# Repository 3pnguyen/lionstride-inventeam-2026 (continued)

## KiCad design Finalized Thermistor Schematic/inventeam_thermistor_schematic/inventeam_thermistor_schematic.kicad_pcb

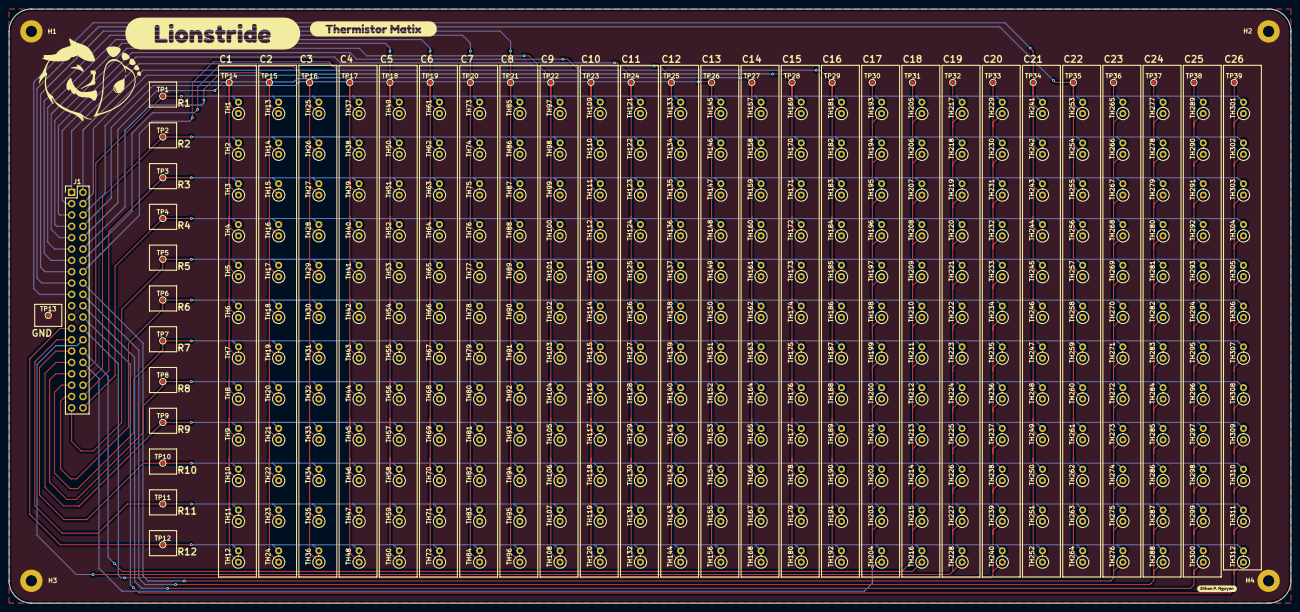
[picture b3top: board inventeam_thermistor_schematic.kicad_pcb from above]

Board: 2 copper layers, 287.0 x 133.0 mm, 359 parts (0 on the bottom side), 39 nets.

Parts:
H1, H2, H3, H4: Mounting Hole; MountingHole_2.5mm_Pad
J1: Header; PinHeader_2x20_P2.54mm_Vertical
TH1, TH2, TH3, TH4, TH5, TH6, TH7, TH8, TH9, TH10, TH11, TH12, TH13, TH14, TH15, TH16, TH17, TH18, TH19, TH20, TH21, TH22, TH23, TH24, TH25, TH26, TH27, TH28, TH29, TH30, TH31, TH32, TH33, TH34, TH35, TH36, TH37, TH38, TH39, TH40, TH41, TH42, TH43, TH44, TH45, TH46, TH47, TH48, TH49, TH50, TH51, TH52, TH53, TH54, TH55, TH56, TH57, TH58, TH59, TH60, TH61, TH62, TH63, TH64, TH65, TH66, TH67, TH68, TH69, TH70, TH71, TH72, TH73, TH74, TH75, TH76, TH77, TH78, TH79, TH80, TH81, TH82, TH83, TH84, TH85, TH86, TH87, TH88, TH89, TH90, TH91, TH92, TH93, TH94, TH95, TH96, TH97, TH98, TH99, TH100, TH101, TH102, TH103, TH104, TH105, TH106, TH107, TH108, TH109, TH110, TH111, TH112, TH113, TH114, TH115, TH116, TH117, TH118, TH119, TH120, TH121, TH122, TH123, TH124, TH125, TH126, TH127, TH128, TH129, TH130, TH131, TH132, TH133, TH134, TH135, TH136, TH137, TH138, TH139, TH140, TH141, TH142, TH143, TH144, TH145, TH146, TH147, TH148, TH149, TH150, TH151, TH152, TH153, TH154, TH155, TH156, TH157, TH158, TH159, TH160, TH161, TH162, TH163, TH164, TH165, TH166, TH167, TH168, TH169, TH170, TH171, TH172, TH173, TH174, TH175, TH176, TH177, TH178, TH179, TH180, TH181, TH182, TH183, TH184, TH185, TH186, TH187, TH188, TH189, TH190, TH191, TH192, TH193, TH194, TH195, TH196, TH197, TH198, TH199, TH200, TH201, TH202, TH203, TH204, TH205, TH206, TH207, TH208, TH209, TH210, TH211, TH212, TH213, TH214, TH215, TH216, TH217, TH218, TH219, TH220, TH221, TH222, TH223, TH224, TH225, TH226, TH227, TH228, TH229, TH230, TH231, TH232, TH233, TH234, TH235, TH236, TH237, TH238, TH239, TH240, TH241, TH242, TH243, TH244, TH245, TH246, TH247, TH248, TH249, TH250, TH251, TH252, TH253, TH254, TH255, TH256, TH257, TH258, TH259, TH260, TH261, TH262, TH263, TH264, TH265, TH266, TH267, TH268, TH269, TH270, TH271, TH272, TH273, TH274, TH275, TH276, TH277, TH278, TH279, TH280, TH281, TH282, TH283, TH284, TH285, TH286, TH287, TH288, TH289, TH290, TH291, TH292, TH293, TH294, TH295, TH296, TH297, TH298, TH299, TH300, TH301, TH302, TH303, TH304, TH305, TH306, TH307, TH308, TH309, TH310, TH311, TH312: 10k; R_Axial_DIN0207_L6.3mm_D2.5mm_P2.54mm_Vertical
TP1, TP2, TP3, TP4, TP5, TP6, TP7, TP8, TP9, TP10, TP11, TP12, TP13, TP14, TP15, TP16, TP17, TP18, TP19, TP20, TP21, TP22, TP23, TP24, TP25, TP26, TP27, TP28, TP29, TP30, TP31, TP32, TP33, TP34, TP35, TP36, TP37, TP38, TP39: TestPoint_Probe; TestPoint_Pad_D1.0mm
kibuzzard-69C4C7E1: G***; kibuzzard-69C4C7E1
kibuzzard-69C4C75F: G***; kibuzzard-69C4C75F
kibuzzard-69C4C905: G***; kibuzzard-69C4C905

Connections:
COLUMN_1: J1.10, TH1.1, TH2.1, TH3.1, TH4.1, TH5.1, TH6.1, TH7.1, TH8.1, TH9.1, TH10.1, TH11.1, TH12.1, TP14.1
COLUMN_2: J1.12, TH13.1, TH14.1, TH15.1, TH16.1, TH17.1, TH18.1, TH19.1, TH20.1, TH21.1, TH22.1, TH23.1, TH24.1, TP15.1
COLUMN_3: J1.14, TH25.1, TH26.1, TH27.1, TH28.1, TH29.1, TH30.1, TH31.1, TH32.1, TH33.1, TH34.1, TH35.1, TH36.1, TP16.1
COLUMN_4: J1.16, TH37.1, TH38.1, TH39.1, TH40.1, TH41.1, TH42.1, TH43.1, TH44.1, TH45.1, TH46.1, TH47.1, TH48.1, TP17.1
COLUMN_5: J1.9, TH49.1, TH50.1, TH51.1, TH52.1, TH53.1, TH54.1, TH55.1, TH56.1, TH57.1, TH58.1, TH59.1, TH60.1, TP18.1
COLUMN_6: J1.11, TH61.1, TH62.1, TH63.1, TH64.1, TH65.1, TH66.1, TH67.1, TH68.1, TH69.1, TH70.1, TH71.1, TH72.1, TP19.1
COLUMN_7: J1.13, TH73.1, TH74.1, TH75.1, TH76.1, TH77.1, TH78.1, TH79.1, TH80.1, TH81.1, TH82.1, TH83.1, TH84.1, TP20.1
COLUMN_8: J1.15, TH85.1, TH86.1, TH87.1, TH88.1, TH89.1, TH90.1, TH91.1, TH92.1, TH93.1, TH94.1, TH95.1, TH96.1, TP21.1
COLUMN_9: J1.7, TH97.1, TH98.1, TH99.1, TH100.1, TH101.1, TH102.1, TH103.1, TH104.1, TH105.1, TH106.1, TH107.1, TH108.1, TP22.1
COLUMN_10: J1.5, TH109.1, TH110.1, TH111.1, TH112.1, TH113.1, TH114.1, TH115.1, TH116.1, TH117.1, TH118.1, TH119.1, TH120.1, TP23.1
COLUMN_11: J1.3, TH121.1, TH122.1, TH123.1, TH124.1, TH125.1, TH126.1, TH127.1, TH128.1, TH129.1, TH130.1, TH131.1, TH132.1, TP24.1
COLUMN_12: J1.1, TH133.1, TH134.1, TH135.1, TH136.1, TH137.1, TH138.1, TH139.1, TH140.1, TH141.1, TH142.1, TH143.1, TH144.1, TP25.1
COLUMN_13: J1.8, TH145.1, TH146.1, TH147.1, TH148.1, TH149.1, TH150.1, TH151.1, TH152.1, TH153.1, TH154.1, TH155.1, TH156.1, TP26.1
COLUMN_14: J1.6, TH157.1, TH158.1, TH159.1, TH160.1, TH161.1, TH162.1, TH163.1, TH164.1, TH165.1, TH166.1, TH167.1, TH168.1, TP27.1
COLUMN_15: J1.4, TH169.1, TH170.1, TH171.1, TH172.1, TH173.1, TH174.1, TH175.1, TH176.1, TH177.1, TH178.1, TH179.1, TH180.1, TP28.1
COLUMN_16: J1.2, TH181.1, TH182.1, TH183.1, TH184.1, TH185.1, TH186.1, TH187.1, TH188.1, TH189.1, TH190.1, TH191.1, TH192.1, TP29.1
COLUMN_17: J1.32, TH193.1, TH194.1, TH195.1, TH196.1, TH197.1, TH198.1, TH199.1, TH200.1, TH201.1, TH202.1, TH203.1, TH204.1, TP30.1
COLUMN_18: J1.30, TH205.1, TH206.1, TH207.1, TH208.1, TH209.1, TH210.1, TH211.1, TH212.1, TH213.1, TH214.1, TH215.1, TH216.1, TP31.1
COLUMN_19: J1.28, TH217.1, TH218.1, TH219.1, TH220.1, TH221.1, TH222.1, TH223.1, TH224.1, TH225.1, TH226.1, TH227.1, TH228.1, TP32.1
COLUMN_20: J1.26, TH229.1, TH230.1, TH231.1, TH232.1, TH233.1, TH234.1, TH235.1, TH236.1, TH237.1, TH238.1, TH239.1, TH240.1, TP33.1
COLUMN_21: J1.19, TH241.1, TH242.1, TH243.1, TH244.1, TH245.1, TH246.1, TH247.1, TH248.1, TH249.1, TH250.1, TH251.1, TH252.1, TP34.1
COLUMN_22: J1.17, TH253.1, TH254.1, TH255.1, TH256.1, TH257.1, TH258.1, TH259.1, TH260.1, TH261.1, TH262.1, TH263.1, TH264.1, TP35.1
COLUMN_23: J1.18, TH265.1, TH266.1, TH267.1, TH268.1, TH269.1, TH270.1, TH271.1, TH272.1, TH273.1, TH274.1, TH275.1, TH276.1, TP36.1
COLUMN_24: J1.20, TH277.1, TH278.1, TH279.1, TH280.1, TH281.1, TH282.1, TH283.1, TH284.1, TH285.1, TH286.1, TH287.1, TH288.1, TP37.1
COLUMN_25: J1.22, TH289.1, TH290.1, TH291.1, TH292.1, TH293.1, TH294.1, TH295.1, TH296.1, TH297.1, TH298.1, TH299.1, TH300.1, TP38.1
COLUMN_26: J1.24, TH301.1, TH302.1, TH303.1, TH304.1, TH305.1, TH306.1, TH307.1, TH308.1, TH309.1, TH310.1, TH311.1, TH312.1, TP39.1
GND: H1.1, H2.1, H3.1, H4.1, J1.23, TP13.1
ROW_1: J1.34, TH1.2, TH13.2, TH25.2, TH37.2, TH49.2, TH61.2, TH73.2, TH85.2, TH97.2, TH109.2, TH121.2, TH133.2, TH145.2, TH157.2, TH169.2, TH181.2, TH193.2, TH205.2, TH217.2, TH229.2, TH241.2, TH253.2, TH265.2, TH277.2, TH289.2, TH301.2, TP1.1
ROW_2: J1.36, TH2.2, TH14.2, TH26.2, TH38.2, TH50.2, TH62.2, TH74.2, TH86.2, TH98.2, TH110.2, TH122.2, TH134.2, TH146.2, TH158.2, TH170.2, TH182.2, TH194.2, TH206.2, TH218.2, TH230.2, TH242.2, TH254.2, TH266.2, TH278.2, TH290.2, TH302.2, TP2.1
ROW_3: J1.38, TH3.2, TH15.2, TH27.2, TH39.2, TH51.2, TH63.2, TH75.2, TH87.2, TH99.2, TH111.2, TH123.2, TH135.2, TH147.2, TH159.2, TH171.2, TH183.2, TH195.2, TH207.2, TH219.2, TH231.2, TH243.2, TH255.2, TH267.2, TH279.2, TH291.2, TH303.2, TP3.1
ROW_4: J1.40, TH4.2, TH16.2, TH28.2, TH40.2, TH52.2, TH64.2, TH76.2, TH88.2, TH100.2, TH112.2, TH124.2, TH136.2, TH148.2, TH160.2, TH172.2, TH184.2, TH196.2, TH208.2, TH220.2, TH232.2, TH244.2, TH256.2, TH268.2, TH280.2, TH292.2, TH304.2, TP4.1
ROW_5: J1.39, TH5.2, TH17.2, TH29.2, TH41.2, TH53.2, TH65.2, TH77.2, TH89.2, TH101.2, TH113.2, TH125.2, TH137.2, TH149.2, TH161.2, TH173.2, TH185.2, TH197.2, TH209.2, TH221.2, TH233.2, TH245.2, TH257.2, TH269.2, TH281.2, TH293.2, TH305.2, TP5.1
ROW_6: J1.37, TH6.2, TH18.2, TH30.2, TH42.2, TH54.2, TH66.2, TH78.2, TH90.2, TH102.2, TH114.2, TH126.2, TH138.2, TH150.2, TH162.2, TH174.2, TH186.2, TH198.2, TH210.2, TH222.2, TH234.2, TH246.2, TH258.2, TH270.2, TH282.2, TH294.2, TH306.2, TP6.1
ROW_7: J1.35, TH7.2, TH19.2, TH31.2, TH43.2, TH55.2, TH67.2, TH79.2, TH91.2, TH103.2, TH115.2, TH127.2, TH139.2, TH151.2, TH163.2, TH175.2, TH187.2, TH199.2, TH211.2, TH223.2, TH235.2, TH247.2, TH259.2, TH271.2, TH283.2, TH295.2, TH307.2, TP7.1
ROW_8: J1.33, TH8.2, TH20.2, TH32.2, TH44.2, TH56.2, TH68.2, TH80.2, TH92.2, TH104.2, TH116.2, TH128.2, TH140.2, TH152.2, TH164.2, TH176.2, TH188.2, TH200.2, TH212.2, TH224.2, TH236.2, TH248.2, TH260.2, TH272.2, TH284.2, TH296.2, TH308.2, TP8.1
ROW_9: J1.31, TH9.2, TH21.2, TH33.2, TH45.2, TH57.2, TH69.2, TH81.2, TH93.2, TH105.2, TH117.2, TH129.2, TH141.2, TH153.2, TH165.2, TH177.2, TH189.2, TH201.2, TH213.2, TH225.2, TH237.2, TH249.2, TH261.2, TH273.2, TH285.2, TH297.2, TH309.2, TP9.1
ROW_10: J1.29, TH10.2, TH22.2, TH34.2, TH46.2, TH58.2, TH70.2, TH82.2, TH94.2, TH106.2, TH118.2, TH130.2, TH142.2, TH154.2, TH166.2, TH178.2, TH190.2, TH202.2, TH214.2, TH226.2, TH238.2, TH250.2, TH262.2, TH274.2, TH286.2, TH298.2, TH310.2, TP10.1
ROW_11: J1.27, TH11.2, TH23.2, TH35.2, TH47.2, TH59.2, TH71.2, TH83.2, TH95.2, TH107.2, TH119.2, TH131.2, TH143.2, TH155.2, TH167.2, TH179.2, TH191.2, TH203.2, TH215.2, TH227.2, TH239.2, TH251.2, TH263.2, TH275.2, TH287.2, TH299.2, TH311.2, TP11.1
ROW_12: J1.25, TH12.2, TH24.2, TH36.2, TH48.2, TH60.2, TH72.2, TH84.2, TH96.2, TH108.2, TH120.2, TH132.2, TH144.2, TH156.2, TH168.2, TH180.2, TH192.2, TH204.2, TH216.2, TH228.2, TH240.2, TH252.2, TH264.2, TH276.2, TH288.2, TH300.2, TH312.2, TP12.1

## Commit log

2026-02-03 Update README with branch information
    Added information about branches and their contents.
2026-02-03 Update README for Lionstride Inventeam project
2026-02-03 Update README with changelog for code versions
    Added changelog for code updates and improvements.
2026-02-03 Update README to include resources in description
2026-02-03 Enhance README with layout and website information
    Added layout and team sections to README.
2026-02-03 Added main code
2026-02-03 Document major switch to PlatformIO in README
2026-02-03 Add note for schematic finalization
    Added note about finalizing schematic.
2026-02-03 Add .gitignore for KiCad project files
2026-02-03 Update README with version timestamps
    Add version timestamps section to README
2026-02-03 Update README with branch description
    Added a branch description for the source code.
2026-02-03 Add branch description for schematic files
    Added a branch description for schematic files.
2026-02-03 Update README with version timestamps
    Added version timestamps for schematic updates.
2026-02-07 Remove v15 minor 1 entry from README
2026-02-07 Delete .gitignore
    KiCad templates already have one
2026-02-07 Update section title for version timestamps
2026-02-07 Added KiCad files
2026-02-14 Change 1uf to 10uf
2026-02-14 Add v15 minor 1 version to README
2026-02-14 Fixed fragmentation w/ more test code
2026-02-14 Update README with memory fragmentation fix
    Added a new entry for memory fragmentation fix and additional test code.
2026-02-18 Refined test code
2026-02-19 Added teeny bit more debug code
2026-02-19 Add test code improvements entry to README
2026-02-19 Tested and slightly modified code
2026-02-19 Even more test code
2026-02-20 Minor fix on row header
2026-02-21 Seperate file for test code
2026-02-21 Moved macros and adjusted test code
2026-02-21 Debug code for expander and multiplexer
2026-02-21 Update README with recent changes and clarifications
2026-02-23 Changed switch time + changed test code
2026-02-23 Schematic V16
2026-02-23 Increased switch time
2026-02-23 Reduce SWITCH_TIME from 15000 to 14000 microseconds
2026-02-23 Converted FSR code and added pull-down macros
2026-02-23 Added pull-down compensation code
2026-02-23 Remove redundant comment in readPressureResistance function
    Removed unnecessary comment regarding offset impact.
2026-02-24 Fixed and tested conversion math
2026-02-24 Change reference IC value
2026-02-24 Overloaded most functions to exclude calibration
2026-02-24 Finished overloading and applied it
2026-02-25 Modified indivudal scan to exclude calibration
2026-02-26 Thank you Allen Iverson
2026-02-26 Added more user input to test code
2026-02-26 Moved macros and prepared new matrix indexing
2026-02-26 Removed maxColumn and maxRow
2026-02-26 Added tech stack
2026-02-26 Moved tech stack
2026-02-26 Slight README format adjustment
2026-02-26 Wrote more for new indexing cod
2026-02-27 Finished indexing code
2026-02-27 Applied row indexing
2026-02-27 Added C in tech stack
2026-02-27 Added debounce
2026-02-27 Fixed timing logic in pressure scanning
2026-02-27 Update README to specify firmware for ESP32s
2026-02-27 Fixed and addded more debouncing
2026-02-27 Fixed time calculation for pressure
2026-02-28 Modded test code for website
2026-02-28 Added forgotten n
2026-02-28 Update 2.27 + extra serial message
2026-03-01 Revise README for debugger UI/website branch
    Updated README to reflect changes in project focus and added images.
2026-03-01 Enhance README with purpose and changelog
    Added purpose and changelog sections to README.md.
2026-03-01 Update README with badges and purpose clarification
    Added badges for CSS3, HTML5, and JavaScript to the README. Updated purpose section for clarity.
2026-03-01 Add images section to README
    Added images section with two images to README.
2026-03-01 Reorganize language badges in README.md
    Rearranged the order of language badges in the README.
2026-03-01 Add website source section to README
2026-03-01 Fixed bug in output
2026-03-02 Removed old helper functions to expose macros
2026-03-03 Added seperate conversion files for later
2026-03-03 v16 minor 1
2026-03-03 Revise prototype changelog in README.md
    Updated prototype changelog with detailed version descriptions.
2026-03-03 Enhance prototype changelog with version details
    Updated version descriptions with detailed explanations for each version.
2026-03-03 Seperated pressure code successfully
2026-03-03 Changed sensor to temperature
2026-03-04 Succesfully removed old logic schematics
2026-03-04 Update README.md badges and credits
    Updated badge links and removed the GPRM credit.
2026-03-04 Update README with badges source and changelog info
    Added badges source information and clarified changelog versioning.
2026-03-04 Update README badges and comments
    Updated badge links and removed outdated comment.
2026-03-04 Revise README with badge sources and project purpose
    Updated README to include badge sources and clarify purpose.
2026-03-04 Add KiCad badge to README
2026-03-04 Add KiCad badge to README
    Added KiCad badge to README for better visibility.
2026-03-04 Added function for moved ref. IC
2026-03-04 Removed old ref. IC macro
2026-03-04 Moved SWITCH TIME macro in macro header
2026-03-05 Add purpose section to README
    Added a purpose section explaining the branch's contents.
2026-03-05 Update README with recent changes and new functions
2026-03-05 Fixed bug in test ADC command
2026-03-05 Added clarity for comment and made filtering consistent
2026-03-06 Updated names for better sorting
2026-03-06 Fixed minor logic errors
2026-03-06 Increased timeout for pressure
2026-03-06 More to 3.5
2026-03-09 Partly through update 3.8.26
2026-03-09 Finished update 3.8.26
2026-03-10 Add VS Code badge
2026-03-10 Update README.md for socials
2026-03-11 Fix socials formatting
2026-03-11 Move items to the left in the chart
2026-03-11 Make layout section better w/ table
2026-03-11 Slight reformat
2026-03-11 Fix and improve README
2026-03-11 Remove link for main
2026-03-11 Khang code
2026-03-11 Made socials section cleaner
2026-03-11 Make socials section cleaner
2026-03-11 Spilt tech stack clearer in raw README
2026-03-11 Fix tech stack
2026-03-11 Fixed link
2026-03-12 Test
2026-03-12 Test 2
2026-03-13 Prepare PCB design stage
2026-03-13 Initialize PCB schematic
2026-03-17 Day 2 of PCB work
2026-03-18 Finished USB C input
2026-03-19 Logic PCB V1
2026-03-19 added BOM for v1
2026-03-19 V1 minor 1
2026-03-19 Update latest version in readme
2026-03-20 Prepare for finalized matrix
2026-03-20 Update pull down values for precision 1M resistor
2026-03-20 Ground header pin for thermistor pcb
2026-03-21 Thermistor schematic V1
2026-03-21 Work on PCB for thermistor
2026-03-24 Work on V2 thermistor PCB
2026-03-24 Finishead header connections
2026-03-26 Thermistor finalized V2
2026-03-26 Update logs for thermistor V2
2026-03-27 Clarity for logic schematic + gerber zip
2026-03-27 Improve minor update naming convention
2026-03-27 Update links to latest versions
2026-03-27 Fix link for finalized logic schematic
2026-03-27 Add versions in README
2026-03-28 Logic schematic v1.3
2026-03-28 Fix forgotten 1.2 to 1.3 change
2026-03-28 Fix link for logic schematic v1.3
2026-03-28 Add Onshape to tech stack
    Because of one image lol + the CAD of the design
2026-03-28 Logic schematic v1.4
2026-03-28 Fix link for v1.4
2026-03-29 Logic schematic V1.4+
2026-03-29 Removed extra 0.1uf capacitor
2026-03-29 Work on PCB for logic schematic
2026-03-29 Gerbers 2 for thermistor v2
2026-04-01 Logic schematic V2
2026-04-01 Prepare for alternative version
2026-04-02 Logic schematic V3
2026-04-02 Work on modifying expander code (WIP)
2026-04-03 Almost completed conversion
2026-04-05 Image update
2026-04-05 make images larger
2026-04-05 Image udpate
2026-04-05 Update 4.5.2026 pt 1
2026-04-05 Update 4.5.26 pt 2
2026-04-05 Added GitHub Pages to tech stack
2026-04-06 Update 4.5.25 pt 3
2026-04-06 Add more/new images of the website
2026-04-06 Fixed the name for one of the images
2026-04-06 Update and add images
2026-04-10 Update purpose description
2026-04-10 Initialize finalized pressure schematics
2026-04-11 initialized hierarchal sheets
2026-04-11 Added forgotten thermisor cell image
2026-04-11 Worked on V1
2026-04-12 Apply gitignore for all projects
2026-04-12 Work on V1
2026-04-12 Added missing revision date and title
2026-04-12 Filled in README
2026-04-13 V1 of pressure schematic
2026-04-13 Update README for pressure schematic
2026-04-13 Add SQLite to tech stack
2026-04-13 Add SQLite badge to README
    Added SQLite badge to the README for better visibility.
2026-04-15 Add description of the Footbox invention
    Added a description section detailing the Footbox invention and its functionality.
2026-04-16 Update README with new documentation and social links
    Reorganize README sections and add DeepWiki badge.
2026-04-16 Add Gallery section to README
    Added a Gallery section with an image to the README.
2026-04-18 Update 4.17.26 part 2
2026-04-18 Remove documentation description
2026-04-18 Update 4.18.26 pt 2
2026-04-24 Updated name of invention
2026-04-28 Duped prototype VD schematic
2026-04-28 Update REAMDE following duped prototype
2026-04-29 Removed finalized pressure v1 in favor of v2
2026-04-29 Update README following last update
2026-04-30 Pressure Schematic V02
2026-04-30 Update README following pressure V2
2026-05-01 Add Inkscape file for pressure m.
2026-05-03 Pressure V2.1
2026-05-03 Fixed link for V2.1
2026-05-03 Added forgotten image of V2.1
2026-05-03 Add Inkscape + clean README
2026-05-03 Added Inkscape to tech stack
2026-05-03 Cleaned README
2026-05-03 Fixed header
2026-05-04 Pressure V2.2
2026-05-04 Gerbers for pressure V2.2
2026-05-05 Seperated changelogs
2026-05-15 Added file for CAD
2026-05-15 Improved file for CAD w/ silkscreen, etc.
2026-05-16 Removed step file because too large + update gitignore
2026-05-20 Update 5.19.26 2
